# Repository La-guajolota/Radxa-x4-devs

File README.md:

# 🚀 Radxa X4 Developers Hub 🚀

<p align="center">
  Your one-stop shop for open-source and open-hardware development for the <strong>Radxa X4 Single-Board Computer</strong>.
</p>

---

## 🌟 About This Project

This repository is a community-driven initiative to provide a comprehensive toolkit for the Radxa X4, centered around a custom-built **Communications HAT**. Our mission is to empower developers, hobbyists, and students to learn, create, and innovate with this powerful SBC.

> 💬 **Motto:** *Building, sharing, and learning together.*

---

## ✨ Key Features

### Hardware 🛠️
-   **Open-Hardware Communications HAT**: A versatile HAT designed for the Radxa X4, with the KiCad project files available in the `Radxa_HAT_communications/hardware` directory.

### Software 💻
-   **Rich Software Examples**: A growing collection of examples for various communication protocols:
    -   **CoAP**: Client and server demonstrations.
    -   **Modbus**: TCP and RTU examples, including a web-based HMI.
    -   **OTA**: A tutorial on secure Over-the-Air firmware updates.
    -   **MQTT, LoRa, CAN**: Placeholders for upcoming examples.

### Mechanical 🔩
-   **CAD Files**: A dedicated directory for 3D models of the HAT and other mechanical components.

---

## 📂 Repository Structure

```
/
├── LICENSE
├── README.md
└── Radxa_HAT_communications/
    ├── CAD/
    ├── hardware/
    └── software/
        ├── Can/
        ├── CoAp/
        ├── LoRa/
        ├── Modbus/
        ├── MQTT/
        └── OTA/
```

---

## 🚀 Getting Started

### Prerequisites

-   A **Radxa X4** board.
-   Basic knowledge of Linux and command-line tools.

### Hardware Setup

To build your own Communications HAT, you can use the KiCad files located in `Radxa_HAT_communications/hardware`. You will need to source the components and manufacture the PCB.

### Software Setup

1.  **Clone the repository**:
    ```bash
    git clone https://github.com/adrianSlpalafox/Radxa-x4-devs.git
    cd Radxa-x4-devs
    ```

2.  **Explore the examples**:
    Navigate to the `Radxa_HAT_communications/software` directory. Each protocol has its own folder with a detailed `README.md`.

3.  **Install dependencies**:
    -   For the **C examples**, you'll likely need `libmodbus`:
        ```bash
        sudo apt-get update
        sudo apt-get install libmodbus-dev build-essential
        ```
    -   For the **Python examples**, check the `README.md` in the respective directory for `pip` install instructions.

---

## 🤝 How to Contribute

We welcome contributions from the community! Whether it's a bug fix, a new feature, or a new example, your help is appreciated.

1.  **Fork** the repository.
2.  Create a new **branch** for your feature (`git checkout -b feature/YourFeature`).
3.  **Commit** your changes (`git commit -m 'Add some feature'`).
4.  **Push** to the branch (`git push origin feature/YourFeature`).
5.  Open a **Pull Request**.

---

## 📄 License

This project is licensed under the terms specified in the `LICENSE` file. Please see the `LICENSE` file for more details.

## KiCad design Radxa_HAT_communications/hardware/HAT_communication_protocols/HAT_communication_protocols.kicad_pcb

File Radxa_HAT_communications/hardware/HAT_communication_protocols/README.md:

# 🛠️ KiCad Project: HAT Communication Protocols

This directory contains the complete **KiCad** project for the Radxa Communications HAT.

---

## 📂 Project Files

Here is a breakdown of the key files in this project:

| File Name                               | Description                                             |
| --------------------------------------- | ------------------------------------------------------- |
| `HAT_communication_protocols.kicad_pro` | 📂 **Main project file**. Open this to start.           |
| `HAT_communication_protocols.kicad_sch` | ⚡ **Schematic file**, containing the circuit diagram.   |
| `HAT_communication_protocols.kicad_pcb` |  LAYOUT **PCB layout file** for component placement. |
| `...-backups/`                          | 💾 Directory for automatic project backups.             |

---

## 🚀 How to Get Started

1.  ### **Install KiCad**
    If you don't have it already, download and install the latest version of KiCad from the official website.
    > 👉 **[kicad.org](https://www.kicad.org/)**

2.  ### **Open the Project**
    -   Launch KiCad.
    -   Navigate to this directory and open the `HAT_communication_protocols.kicad_pro` file.

3.  ### **Explore and Modify**
    -   From the KiCad project manager, you can open the schematic (`.kicad_sch`) and PCB layout (`.kicad_pcb`) to view, analyze, and modify the design.

Happy Designing! ✨

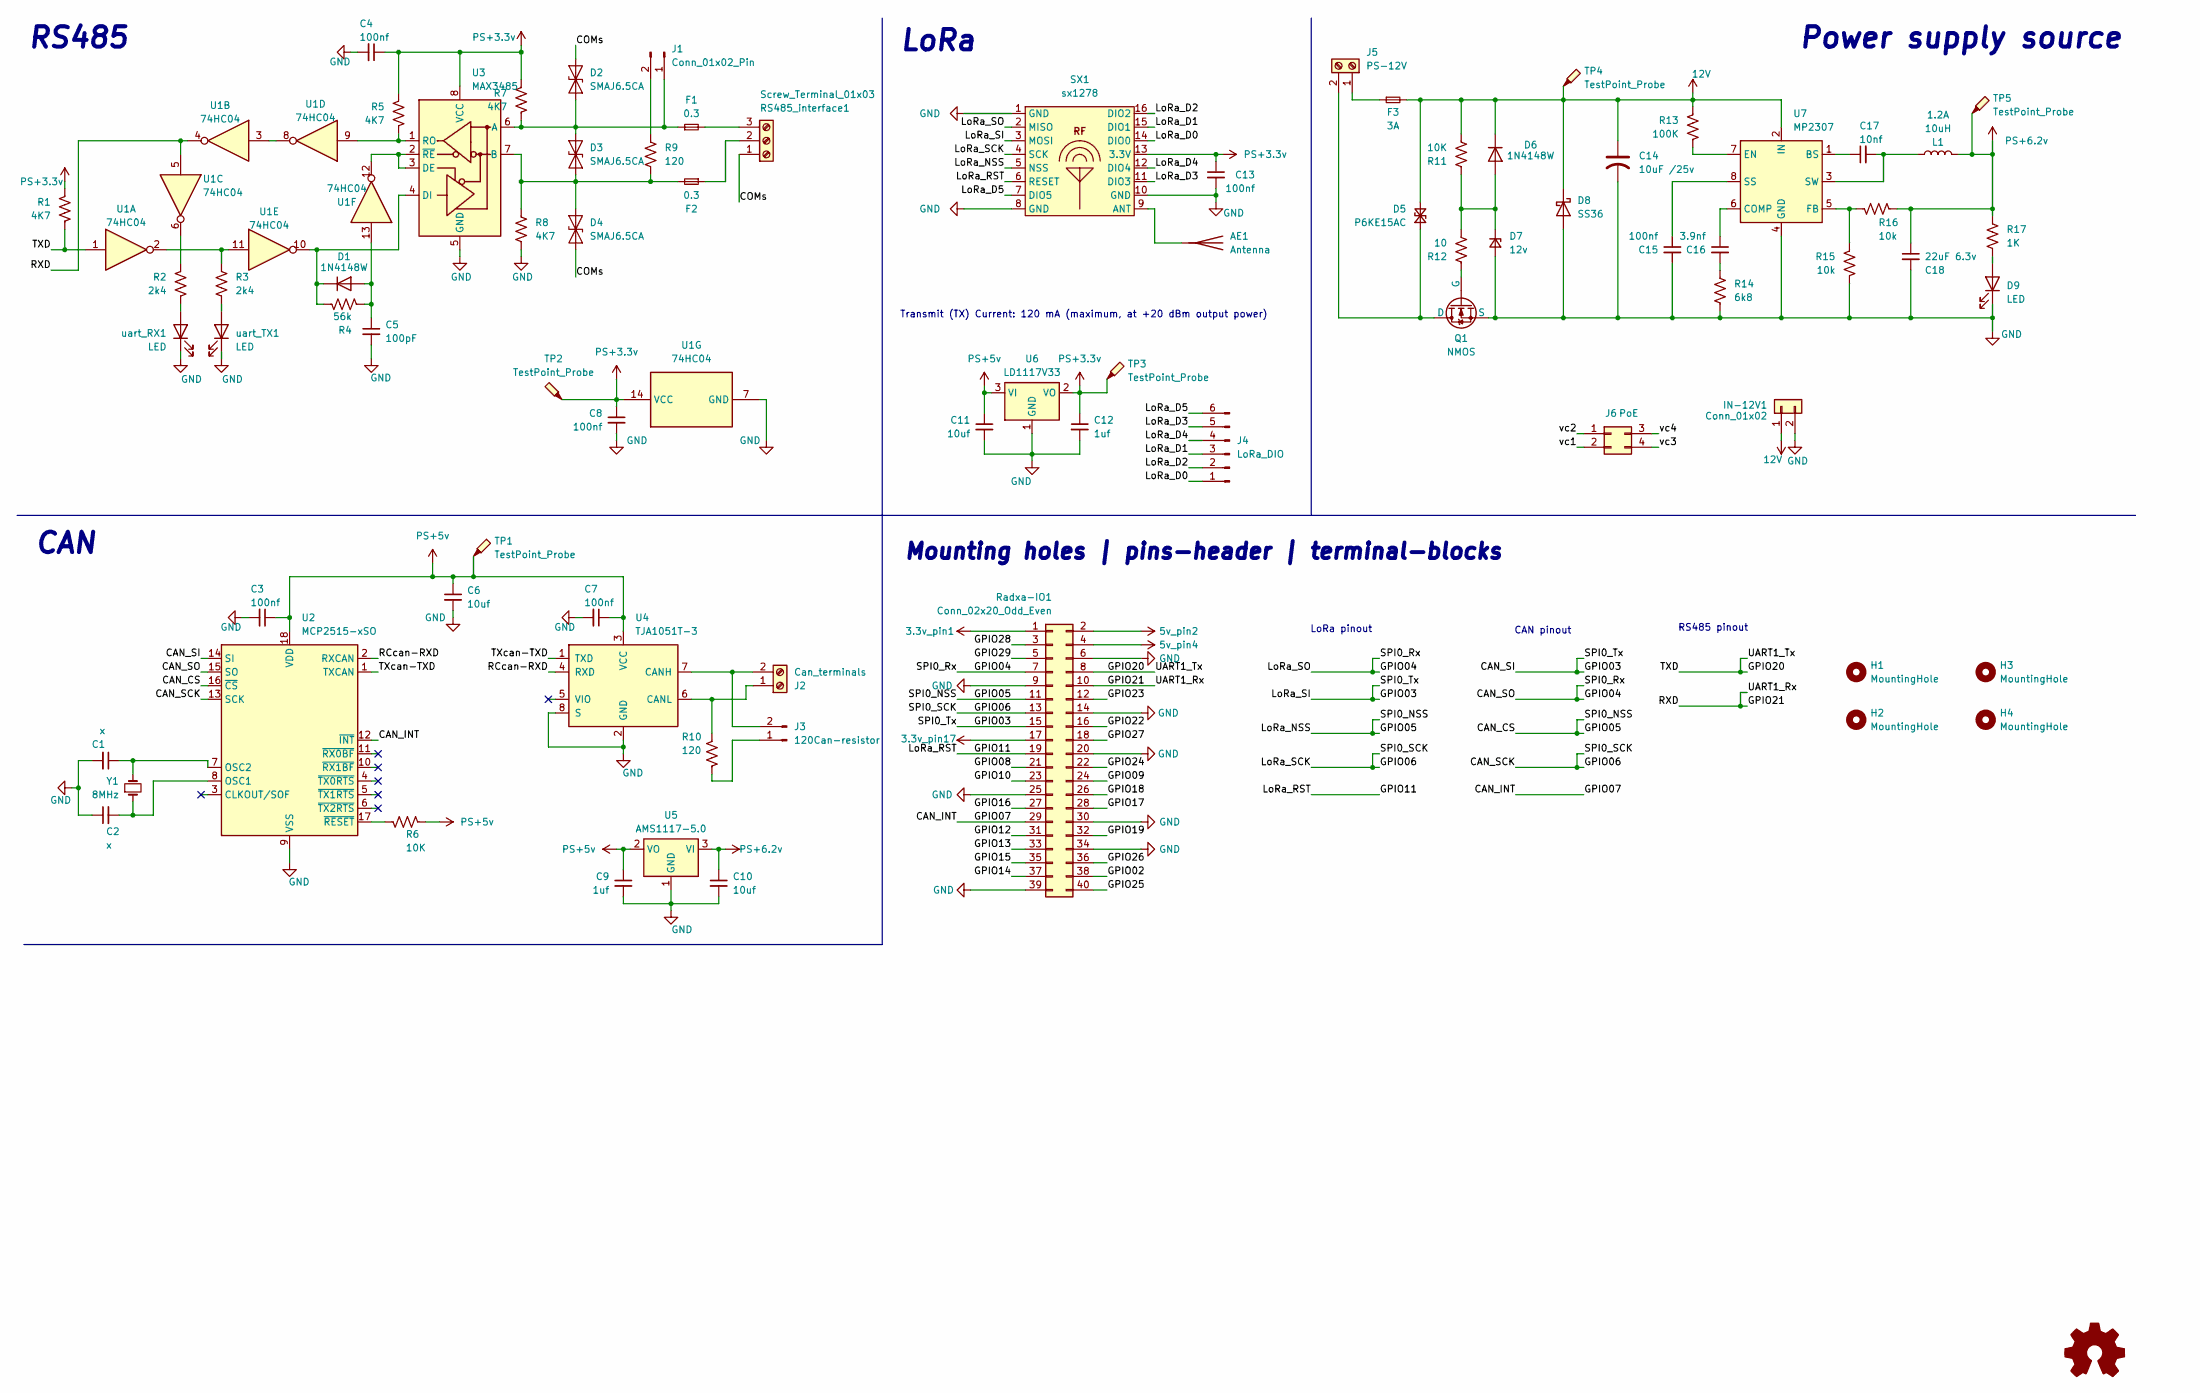
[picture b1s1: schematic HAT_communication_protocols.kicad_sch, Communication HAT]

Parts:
AE1: Antenna; PinHeader_1x01_P2.54mm_Vertical
C1, C2: x; C_0603_1608Metric_Pad1.08x0.95mm_HandSolder
C3, C4, C7, C8, C13, C15: 100nf; R_0603_1608Metric_Pad0.98x0.95mm_HandSolder
C5: 100pF; R_0603_1608Metric_Pad0.98x0.95mm_HandSolder
C6, C10, C11: 10uf; R_0603_1608Metric_Pad0.98x0.95mm_HandSolder
C9, C12: 1uf; R_0603_1608Metric_Pad0.98x0.95mm_HandSolder
C14: 10uF /25v; C_1206_3216Metric_Pad1.33x1.80mm_HandSolder
C16: 3.9nf; R_0603_1608Metric_Pad0.98x0.95mm_HandSolder
C17: 10nf; R_0603_1608Metric_Pad0.98x0.95mm_HandSolder
C18: 22uF 6.3v; C_1206_3216Metric_Pad1.33x1.80mm_HandSolder
D1, D6: 1N4148W; D_SOD-123
D2, D3, D4: SMAJ6.5CA; D_SMA
D5: P6KE15AC; D_DO-15_P12.70mm_Horizontal
D7: 12v; D_MiniMELF_Handsoldering
D8: SS36; D_SMA_Handsoldering
D9: LED; LED_1206_3216Metric_Pad1.42x1.75mm_HandSolder
F1, F2: 0.3; C_1812_4532Metric_Pad1.57x3.40mm_HandSolder
F3: 3A; Fuse_1206_3216Metric_Pad1.42x1.75mm_HandSolder
H1, H2, H3, H4: MountingHole; MountingHole_2.5mm
IN-12V1: Conn_01x02; PinSocket_1x02_P2.54mm_Vertical; Part Number 1-0201FBV0T
J1: Conn_01x02_Pin; PinHeader_1x02_P2.54mm_Vertical
J2: Can_terminals; TerminalBlock_MetzConnect_Type101_RT01602HBWC_1x02_P5.08mm_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
J3: 120Can-resistor; PinHeader_1x02_P2.54mm_Vertical
J4: LoRa_DIO; PinHeader_1x06_P2.54mm_Vertical
J5: PS-12V; TerminalBlock_MetzConnect_Type101_RT01602HBWC_1x02_P5.08mm_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
J6: PoE; PinSocket_2x02_P2.54mm_Vertical
L1: 100uH_1.0A; L_Wuerth_WE-PD-Typ-M-Typ-S_Handsoldering; Part Number NRS4018T100MDGJ
Q1: NMOS; TO-252-2
R1, R5, R7, R8: 4K7; R_0603_1608Metric_Pad0.98x0.95mm_HandSolder
R2, R3: 2k4; R_0603_1608Metric_Pad0.98x0.95mm_HandSolder
R4: 56k; R_0603_1608Metric_Pad0.98x0.95mm_HandSolder
R6, R11: 10K; R_0603_1608Metric_Pad0.98x0.95mm_HandSolder
R9, R10: 120; R_0603_1608Metric_Pad0.98x0.95mm_HandSolder
R12: 10; R_0603_1608Metric_Pad0.98x0.95mm_HandSolder
R13: 100K; R_0603_1608Metric_Pad0.98x0.95mm_HandSolder
R14: 6k8; R_0603_1608Metric_Pad0.98x0.95mm_HandSolder
R15, R16: 10k; R_0603_1608Metric_Pad0.98x0.95mm_HandSolder
R17: 1K; R_0603_1608Metric_Pad0.98x0.95mm_HandSolder
RS485_interface1: Screw_Terminal_01x03; TerminalBlock_MetzConnect_Type101_RT01603HBWC_1x03_P5.08mm_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
Radxa-IO1: Conn_02x20_Odd_Even; PinHeader_2x20_P2.54mm_Vertical
SX1: sx1278; SX1278 module
TP1, TP2, TP3, TP4, TP5: TestPoint_Probe; TestPoint_Pad_D1.0mm
U1: 74HC04; SO-14_3.9x8.65mm_P1.27mm
U2: MCP2515-xSO; SOIC-18W_7.5x11.6mm_P1.27mm
U3: MAX3485; SOIC-8_3.9x4.9mm_P1.27mm
U4: TJA1051T-3; SOIC-8_3.9x4.9mm_P1.27mm
U5: AMS1117-5.0; SOT-223-3_TabPin2
U6: LD1117V33; SOT-223-3_TabPin2
U7: MP2307; SOIC-8-1EP_3.9x4.9mm_P1.27mm_EP2.62x3.51mm
Y1: 8MHz; Crystal_HC18-U_Vertical
uart_RX1: LED; LED_1206_3216Metric_Pad1.42x1.75mm_HandSolder
uart_TX1: LED; LED_1206_3216Metric_Pad1.42x1.75mm_HandSolder

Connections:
12V: C14.1, D5.2 (A2), D6.1 (K), D8.1 (K), F3.2, IN-12V1.1, R11.2, R13.1, TP4.1, U7.2 (IN)
/CAN_CS: Radxa-IO1.11, SX1.5 (NSS), U2.16 (~CS); also elsewhere on the board
/CAN_INT: Radxa-IO1.29, U2.12 (~INT); also elsewhere on the board
/CAN_SCK: Radxa-IO1.13, SX1.4 (SCK), U2.13 (SCK); also elsewhere on the board
/CAN_SI: Radxa-IO1.15, SX1.3 (MOSI), U2.14 (SI); also elsewhere on the board
/CAN_SO: Radxa-IO1.7, SX1.2 (MISO), U2.15 (SO); also elsewhere on the board
/COMs: D2.2 (A2), D4.1 (A1), RS485_interface1.1; also elsewhere on the board
/GPIO11: Radxa-IO1.19, SX1.6 (RESET); also elsewhere on the board
/GPIO20: R1.2, Radxa-IO1.8, U1.1; also elsewhere on the board
/GPIO21: Radxa-IO1.10, U1.4, U1.5; also elsewhere on the board
/LoRa_D0: J4.1, SX1.14 (DIO0)
/LoRa_D1: J4.3, SX1.15 (DIO1)
/LoRa_D2: J4.2, SX1.16 (DIO2)
/LoRa_D3: J4.5, SX1.11 (DIO3)
/LoRa_D4: J4.4, SX1.12 (DIO4)
/LoRa_D5: J4.6, SX1.7 (DIO5)
/RCcan-RXD: U2.2 (RXCAN), U4.4 (RXD)
/TXcan-TXD: U2.1 (TXCAN), U4.1 (TXD)
/vc1: J6.2
/vc2: J6.1
/vc3: J6.4
/vc4: J6.3
GND: C1.2, C2.1, C3.2, C4.2, C5.2, C6.2, C7.2, C8.2, C9.2, C10.2, C11.2, C12.2, C13.2, C14.2, C15.2, C18.2, D7.2 (A), D8.2 (A), D9.1 (K), IN-12V1.2, Q1.3 (S), R8.2, R14.2, R15.2, Radxa-IO1.6, Radxa-IO1.9, Radxa-IO1.14, Radxa-IO1.20, Radxa-IO1.25, Radxa-IO1.30, Radxa-IO1.34, Radxa-IO1.39, SX1.1 (GND), SX1.8 (GND), SX1.10 (GND), U1.7 (GND), U2.9 (VSS), U3.5 (GND), U4.2 (GND), U4.8 (S), U5.1 (GND), U6.1 (GND), U7.4 (GND), uart_RX1.1 (K), uart_TX1.1 (K); also elsewhere on the board
unnamed: AE1.1 (A), SX1.9 (ANT)
unnamed: C16.2, R14.1
unnamed: C5.1, D1.2 (A), R4.2, U1.13
unnamed: D1.1 (K), R4.1, U1.10, U3.4 (DI)
unnamed: D2.1 (A1), D3.2 (A2), F1.1, J1.1, R7.2, U3.6 (A)
unnamed: D3.1 (A1), D4.2 (A2), F2.2, R8.1, R9.2, U3.7 (B)
unnamed 53: D5.1 (A1), J5.2, Q1.2 (D); also elsewhere on the board
unnamed: D6.2 (A), D7.1 (K), R11.1, R12.2
unnamed: D9.2 (A), R17.2
unnamed: J1.2, R9.1
unnamed 57: J2.1, R10.1, U4.6 (CANL); also elsewhere on the board
unnamed 58: J2.2, J3.2, U4.7 (CANH); also elsewhere on the board
unnamed: J3.1, R10.2
unnamed 60: F3.1, J5.1; also elsewhere on the board
unnamed: Q1.1 (G), R12.1
unnamed: R2.1, U1.6
unnamed: R3.1, U1.2, U1.11
unnamed 64: F2.1, RS485_interface1.2; also elsewhere on the board
unnamed 65: F1.2, RS485_interface1.3; also elsewhere on the board
unnamed: U1.3, U1.8
unnamed: C2.2, U2.8 (OSC1), Y1.1
unnamed: C1.1, U2.7 (OSC2), Y1.2
unnamed: R6.1, U2.17 (~RESET)
unnamed: U1.12, U3.2 (~RE), U3.3 (DE)
unnamed: R5.2, U1.9, U3.1 (RO)
unnamed: C17.1, U7.1 (BS)
unnamed: C16.1, U7.6 (COMP)
unnamed: R13.2, U7.7 (EN)
unnamed: R15.1, R16.2, U7.5 (FB)
unnamed: C15.1, U7.8 (SS)
unnamed: C17.2, L1.1, U7.3 (SW)
unnamed 78: R2.2, uart_RX1.2 (A); also elsewhere on the board
unnamed 79: R3.2, uart_TX1.2 (A); also elsewhere on the board
PS+3.3v: C4.1, C8.1, C12.1, C13.1, R1.1, R5.1, R7.1, SX1.13 (3.3V), TP2.1, TP3.1, U1.14 (VCC), U3.8 (VCC), U6.2 (VO)
PS+5v: C3.1, C6.1, C7.1, C9.1, C11.1, R6.2, TP1.1, U2.18 (VDD), U4.3 (VCC), U5.2 (VO), U6.3 (VI)
PS+6.2v: C10.1, C18.1, L1.2, R16.1, R17.1, TP5.1, U5.3 (VI)

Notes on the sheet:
Transmit (TX) Current: 120 mA (maximum, at +20 dBm output power)
LoRa
RS485
Power supply source
Mounting holes | pins-header | terminal-blocks
CAN
CAN pinout
LoRa pinout
RS485 pinout

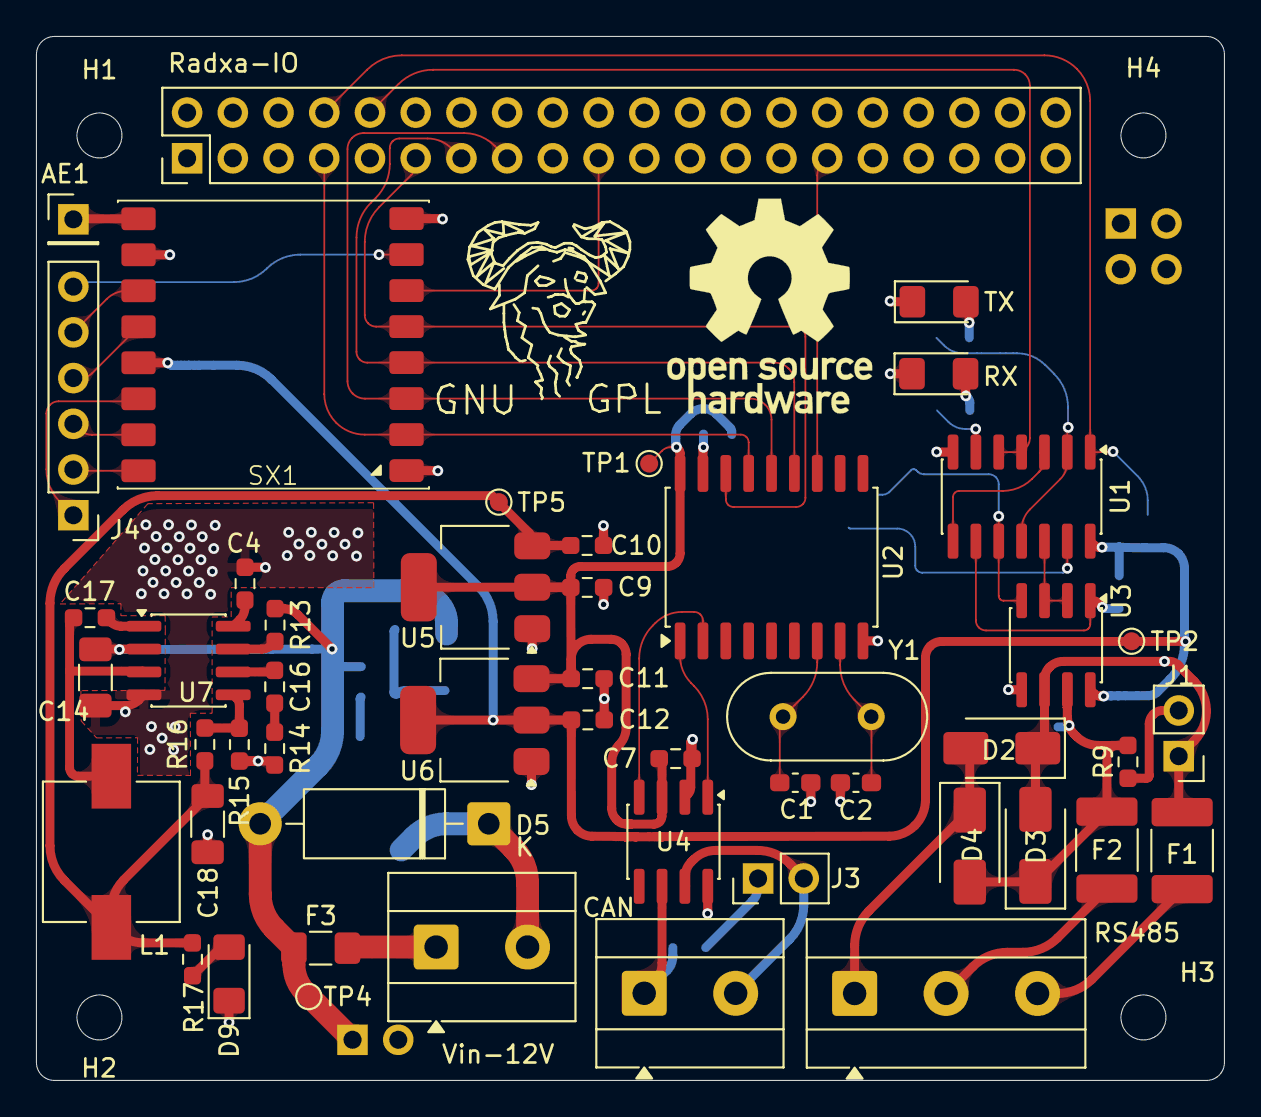
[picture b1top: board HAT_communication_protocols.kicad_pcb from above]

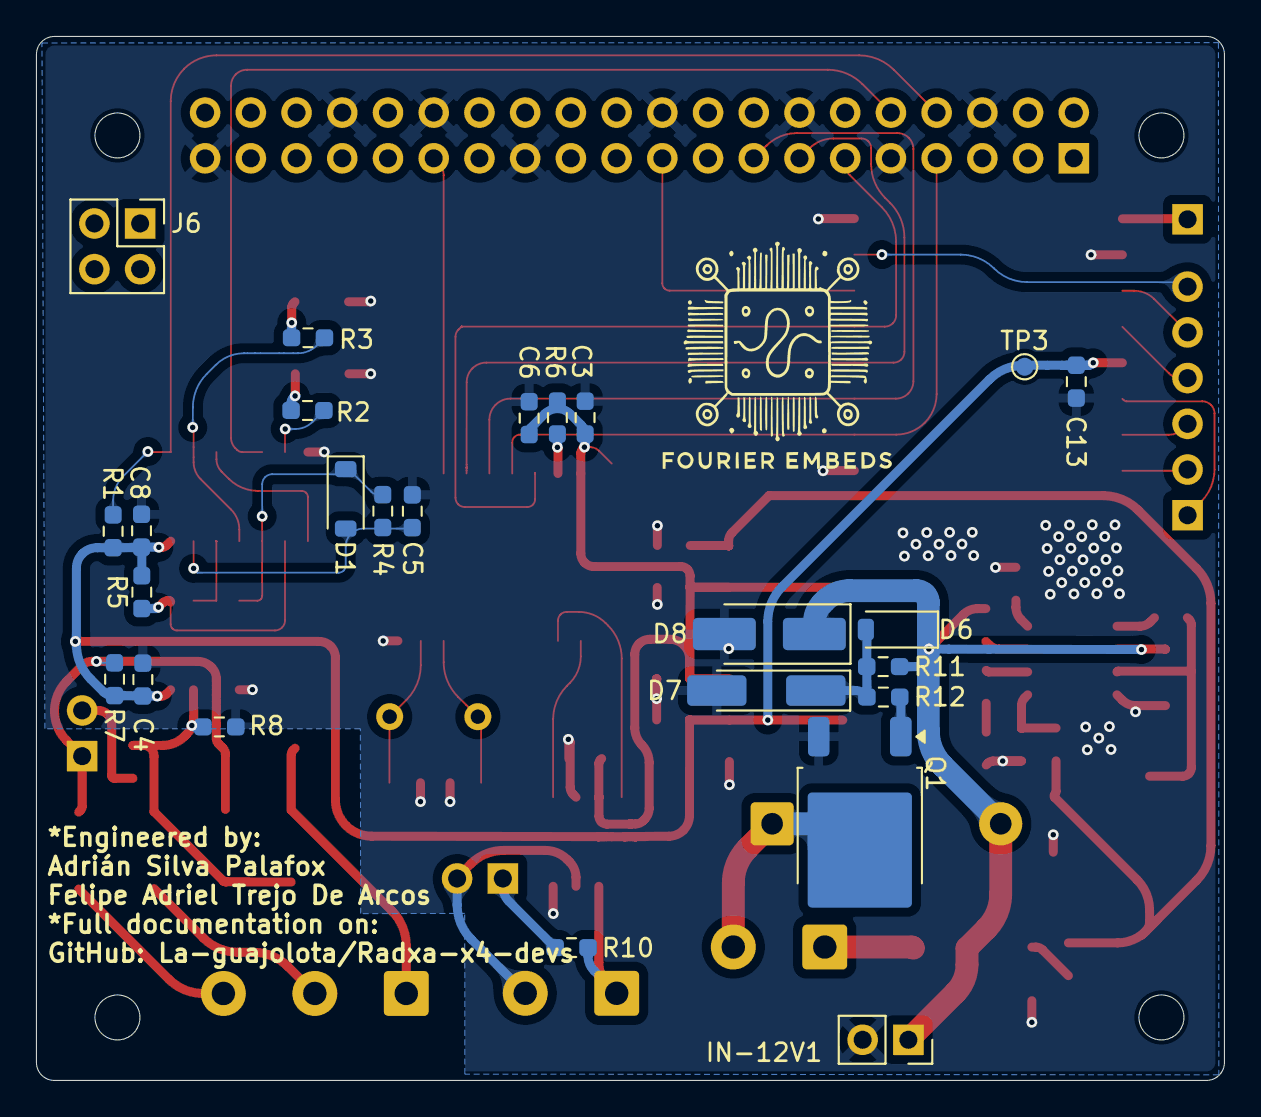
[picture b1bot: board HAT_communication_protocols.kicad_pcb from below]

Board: 2 copper layers, 66.0 x 58.0 mm, 81 parts (26 on the bottom side), 55 nets.

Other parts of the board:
-: Symbol_GNU-Logo_SilkscreenTop
CAN: Can_terminals; TerminalBlock_MetzConnect_Type101_RT01602HBWC_1x02_P5.08mm_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
Engineered by : LOGO; LOGOFOURIEREMBEDS
RS485: Screw_Terminal_01x03; TerminalBlock_MetzConnect_Type101_RT01603HBWC_1x03_P5.08mm_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
RX: LED; LED_1206_3216Metric_Pad1.42x1.75mm_HandSolder
Radxa-IO: Conn_02x20_Odd_Even; PinHeader_2x20_P2.54mm_Vertical
TX: LED; LED_1206_3216Metric_Pad1.42x1.75mm_HandSolder
Vin-12V: PS-12V; TerminalBlock_MetzConnect_Type101_RT01602HBWC_1x02_P5.08mm_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

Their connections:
/CAN_CS: Radxa-IO.11; also elsewhere on the board
/CAN_INT: Radxa-IO.29; also elsewhere on the board
/CAN_SCK: Radxa-IO.13; also elsewhere on the board
/CAN_SI: Radxa-IO.15; also elsewhere on the board
/CAN_SO: Radxa-IO.7; also elsewhere on the board
/COMs: RS485.1; also elsewhere on the board
/GPIO11: Radxa-IO.19; also elsewhere on the board
/GPIO20: Radxa-IO.8; also elsewhere on the board
/GPIO21: Radxa-IO.10; also elsewhere on the board
GND: RX.1 (K), Radxa-IO.6, Radxa-IO.9, Radxa-IO.14, Radxa-IO.20, Radxa-IO.25, Radxa-IO.30, Radxa-IO.34, Radxa-IO.39, TX.1 (K); also elsewhere on the board
unnamed 53: Vin-12V.2; also elsewhere on the board
unnamed 57: CAN.1; also elsewhere on the board
unnamed 58: CAN.2; also elsewhere on the board
unnamed 60: Vin-12V.1; also elsewhere on the board
unnamed 64: RS485.2; also elsewhere on the board
unnamed 65: RS485.3; also elsewhere on the board
unnamed 78: RX.2 (A); also elsewhere on the board
unnamed 79: TX.2 (A); also elsewhere on the board

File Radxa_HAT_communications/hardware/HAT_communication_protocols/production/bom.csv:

Designator,Footprint,Quantity,Value,LCSC Part #
AE1,PinHeader_1x01_P2.54mm_Vertical,1,Antenna,
"C1, C2",0603,2,x,
"C10, C11, C6",0603,3,10uf,
"C12, C9",0603,2,1uf,
"C13, C15, C3, C4, C7, C8",0603,6,100nf,
C14,1206,1,10uF /25v,
C16,0603,1,3.9nf,
C17,0603,1,10nf,
C18,1206,1,22uF 6.3v,
C5,0603,1,100pF,
CAN,TerminalBlock_MetzConnect_Type101_RT01602HBWC_1x02_P5.08mm_Horizontal,1,Can_terminals,
"D1, D6",D_SOD-123,2,1N4148W,
"D2, D3, D4",D_SMA,3,SMAJ6.5CA,
D5,D_DO-15_P12.70mm_Horizontal,1,P6KE15AC,
D7,D_MiniMELF_Handsoldering,1,12v,
D8,D_SMA_Handsoldering,1,SS36,
"D9, RX, TX",1206,3,LED,
"F1, F2",1812,2,0.3,
F3,1206,1,3A,
IN-12V1,PinSocket_1x02_P2.54mm_Vertical,1,Conn_01x02,
J1,PinHeader_1x02_P2.54mm_Vertical,1,Conn_01x02_Pin,
J3,PinHeader_1x02_P2.54mm_Vertical,1,120Can-resistor,
J4,PinHeader_1x06_P2.54mm_Vertical,1,LoRa_DIO,
J6,PinSocket_2x02_P2.54mm_Vertical,1,PoE,
L1,L_Wuerth_WE-PD-Typ-M-Typ-S_Handsoldering,1,100uH_1.0A,
Q1,TO-252-2,1,NMOS,
"R1, R5, R7, R8",0603,4,4K7,
"R10, R9",0603,2,120,
"R11, R15, R16, R6",0603,4,10K,
R12,0603,1,10,
R13,0603,1,100K,
R14,0603,1,6k8,
R17,0603,1,1K,
"R2, R3",0603,2,2k4,
R4,0603,1,56k,
RADXA-IO,PinHeader_2x20_P2.54mm_Vertical,1,Conn_02x20_Odd_Even,
RS485,TerminalBlock_MetzConnect_Type101_RT01603HBWC_1x03_P5.08mm_Horizontal,1,Screw_Terminal_01x03,
SX1,SX1278 module,1,sx1278,
"TP1, TP2, TP3, TP4, TP5",TestPoint_Pad_D1.0mm,5,TestPoint_Probe,
U1,SO-14_3.9x8.65mm_P1.27mm,1,74HC04,
U2,SOIC-18W_7.5x11.6mm_P1.27mm,1,MCP2515-xSO,
U3,SOIC-8_3.9x4.9mm_P1.27mm,1,MAX3485,
U4,SOIC-8_3.9x4.9mm_P1.27mm,1,TJA1051T-3,
U5,SOT-223-3_TabPin2,1,AMS1117-5.0,
U6,SOT-223-3_TabPin2,1,LD1117V33,
U7,SOIC-8-1EP_3.9x4.9mm_P1.27mm_EP2.62x3.51mm,1,MP2307,
VIN-12V,TerminalBlock_MetzConnect_Type101_RT01602HBWC_1x02_P5.08mm_Horizontal,1,PS-12V,
Y1,Crystal_HC18-U_Vertical,1,8MHz,

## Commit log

2025-10-14 Readmes
2025-10-14 Readmes refactor
2025-10-16 new docummentation
2025-10-17 PCB design | PCB countors finally drew and correct placement of pinheaders and pin socker so they fit to the Radxa-X4 form factor
2025-10-18 Placement of some components in PCB layout. Thinking on adding a buck converter
2025-10-19 PCB layout first version done
2025-10-19 PCB tracks 60% completed
2025-10-20 PCB V1 done
2025-10-20 PCB V1.2 done
2025-10-20 PCB V1.3 done
2025-10-20 PCB V1.4 done
2025-10-21 PCB V1.5 done
2025-10-21 Final Review - in production
2025-10-21 documentation updated
2025-10-28 .gitignore added
2025-11-11 VDF-TELEMETRY
2025-11-17 DELTA-MS300-RTU programs
2025-11-24 MQTT client added
2025-11-24 MQTT test client added
2025-11-25 Direction command correction. Already working
